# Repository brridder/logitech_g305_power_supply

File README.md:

# G305 LiPo Buck

This is intended to replace the AA battery in the Logitech G305 mouse, but it could be used to replace any 1.5V battery
with a LiPo. Pick a LiPo based on mass to save the most weight. It doesn't need a crazy high mAh battery to work for
along time. It's a very energy efficient mouse.

It got the weight down from ~88g (no cover, 96g with battery cover) to 67g no cover, 74g with cover. That gets it within
a few grams of the G Pro Superlight. The battery holder needs to be removed to add to the weight savings. There's
probably some more plastics that can be removed to reduce even more weight.

## Why?

I got nerd sniped by my friends. I wanted to prove that chasing reduced weight is pretty dumb and reducing it isn't that
hard. Just focus on the heaviest parts and cut it as much as possible. In this mouse, the heaviest part is the battery
and plastics holding it. It's also the lowest hanging fruit for replacement since it doesn't require modifying how the
main PCBa is held in the plastics. 

It worked pretty well. This doesn't include charge circuitry so the battery has to be
charged out of the mouse. It lasted quite a while. It's been years since I've used this set up, but it worked pretty
well for how janky it is.

It's effectively the buck converter's reference schematic tuned to go to 2.0V or 1.5V based on stuffing options. I
knocked it out in an hour so there's probably room for improvements.

## Future improvements.

* Include charge circuitry w/ USBC
* Shorten the battery leads
* Reduce more weight by removing more plastic. Speed holes!

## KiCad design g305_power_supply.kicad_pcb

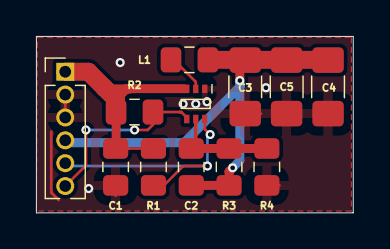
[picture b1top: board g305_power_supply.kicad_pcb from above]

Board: 2 copper layers, 17.6 x 9.8 mm, 12 parts (0 on the bottom side), 7 nets.

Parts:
C1: 15uF; C_0805_2012Metric_Pad1.15x1.40mm_HandSolder
C2: 120pF; C_0805_2012Metric_Pad1.15x1.40mm_HandSolder
C3, C4, C5: 10uF; C_1206_3216Metric_Pad1.42x1.75mm_HandSolder
IC1: TPS62A02; SOTFL50P160X60-6N
J1: Conn_01x02_Female; PinHeader_1x06_P1.27mm_Vertical
L1: 1uH; L_0805_2012Metric_Pad1.15x1.40mm_HandSolder
R1: 499k; R_0805_2012Metric_Pad1.15x1.40mm_HandSolder
R2: 0; R_0805_2012Metric_Pad1.15x1.40mm_HandSolder
R3: 232k; R_0805_2012Metric_Pad1.15x1.40mm_HandSolder
R4: 100k; R_0805_2012Metric_Pad1.15x1.40mm_HandSolder

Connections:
/EN: IC1.4, J1.6, R2.2
/PG: IC1.6, J1.5, R1.2
/V_in: C1.1, IC1.3, J1.1, R1.1, R2.1
/V_out: C2.1, C3.1, C4.1, C5.1, J1.4, L1.2, R3.2
GND: C1.2, C3.2, C4.2, C5.2, IC1.1, J1.2, J1.3, R4.1
unnamed: C2.2, IC1.5, R3.1, R4.2
unnamed: IC1.2, L1.1

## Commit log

2025-09-21 G305 power supply
2025-09-21 Add pictures of the final weights
2025-09-21 add readme
